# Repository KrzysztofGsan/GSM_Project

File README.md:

# GSM Home Controller (AVR) - Work in Progress

## Project Overview
This is an embedded C project developed for the **ATmega16** microcontroller. The primary objective is to create a versatile controller capable of managing electrical outputs based on various inputs, including **SMS commands (GSM module)**, **time-based scheduling (RTC)**, and **sound triggers (Clap Switch)**.

The project demonstrates a hands-on approach to low-level programming and hardware-software interaction in an embedded environment.

## Key Features & Tech Stack
* **State Machine Architecture:** Implemented a robust state machine (`enum Tryb`) to manage multiple operation modes (GSM, Bluetooth, Potentiometer control, Time Scheduling, and Sound Control).
* **Communication Protocols:**
    * **UART:** Integration with a GSM module using AT commands for remote control and message parsing.
    * **I2C (TWI):** Interfacing with a Real-Time Clock (DS1307/similar) for precise time-based output triggering.
* **Peripheral Management:**
    * **ADC:** Used for sound detection (Clap Switch logic) and reading analog values from potentiometers or sensors.
    * **PWM (Fast PWM Mode):** Power output control with adjustable duty cycle.
    * **Interrupts:** Efficient handling of serial data reception (USART_RX) and timer-based tasks (display refreshing).
* **Hardware:** AVR ATmega16, HD44780 LCD, GSM/BT modules, Triac/Relay outputs.
* **Environment:** Developed using **Eclipse IDE with AVR plugin**.

## Current Status
* [x] Hardware abstraction layer for GPIO, PWM, and ADC.
* [x] I2C Communication with RTC and time-matching logic.
* [x] Menu system for manual mode switching via hardware buttons.
* [x] Real-time status reporting on HD44780 LCD.
* [ ] **In Progress:** Refining the circular buffer logic for GSM message parsing and improving ASPICE-aligned documentation for the project.

## How to build
The project is configured for a CPU frequency of **8MHz** (defined in the IDE/Makefile). It requires the `avr-gcc` compiler and `avr-libc`.

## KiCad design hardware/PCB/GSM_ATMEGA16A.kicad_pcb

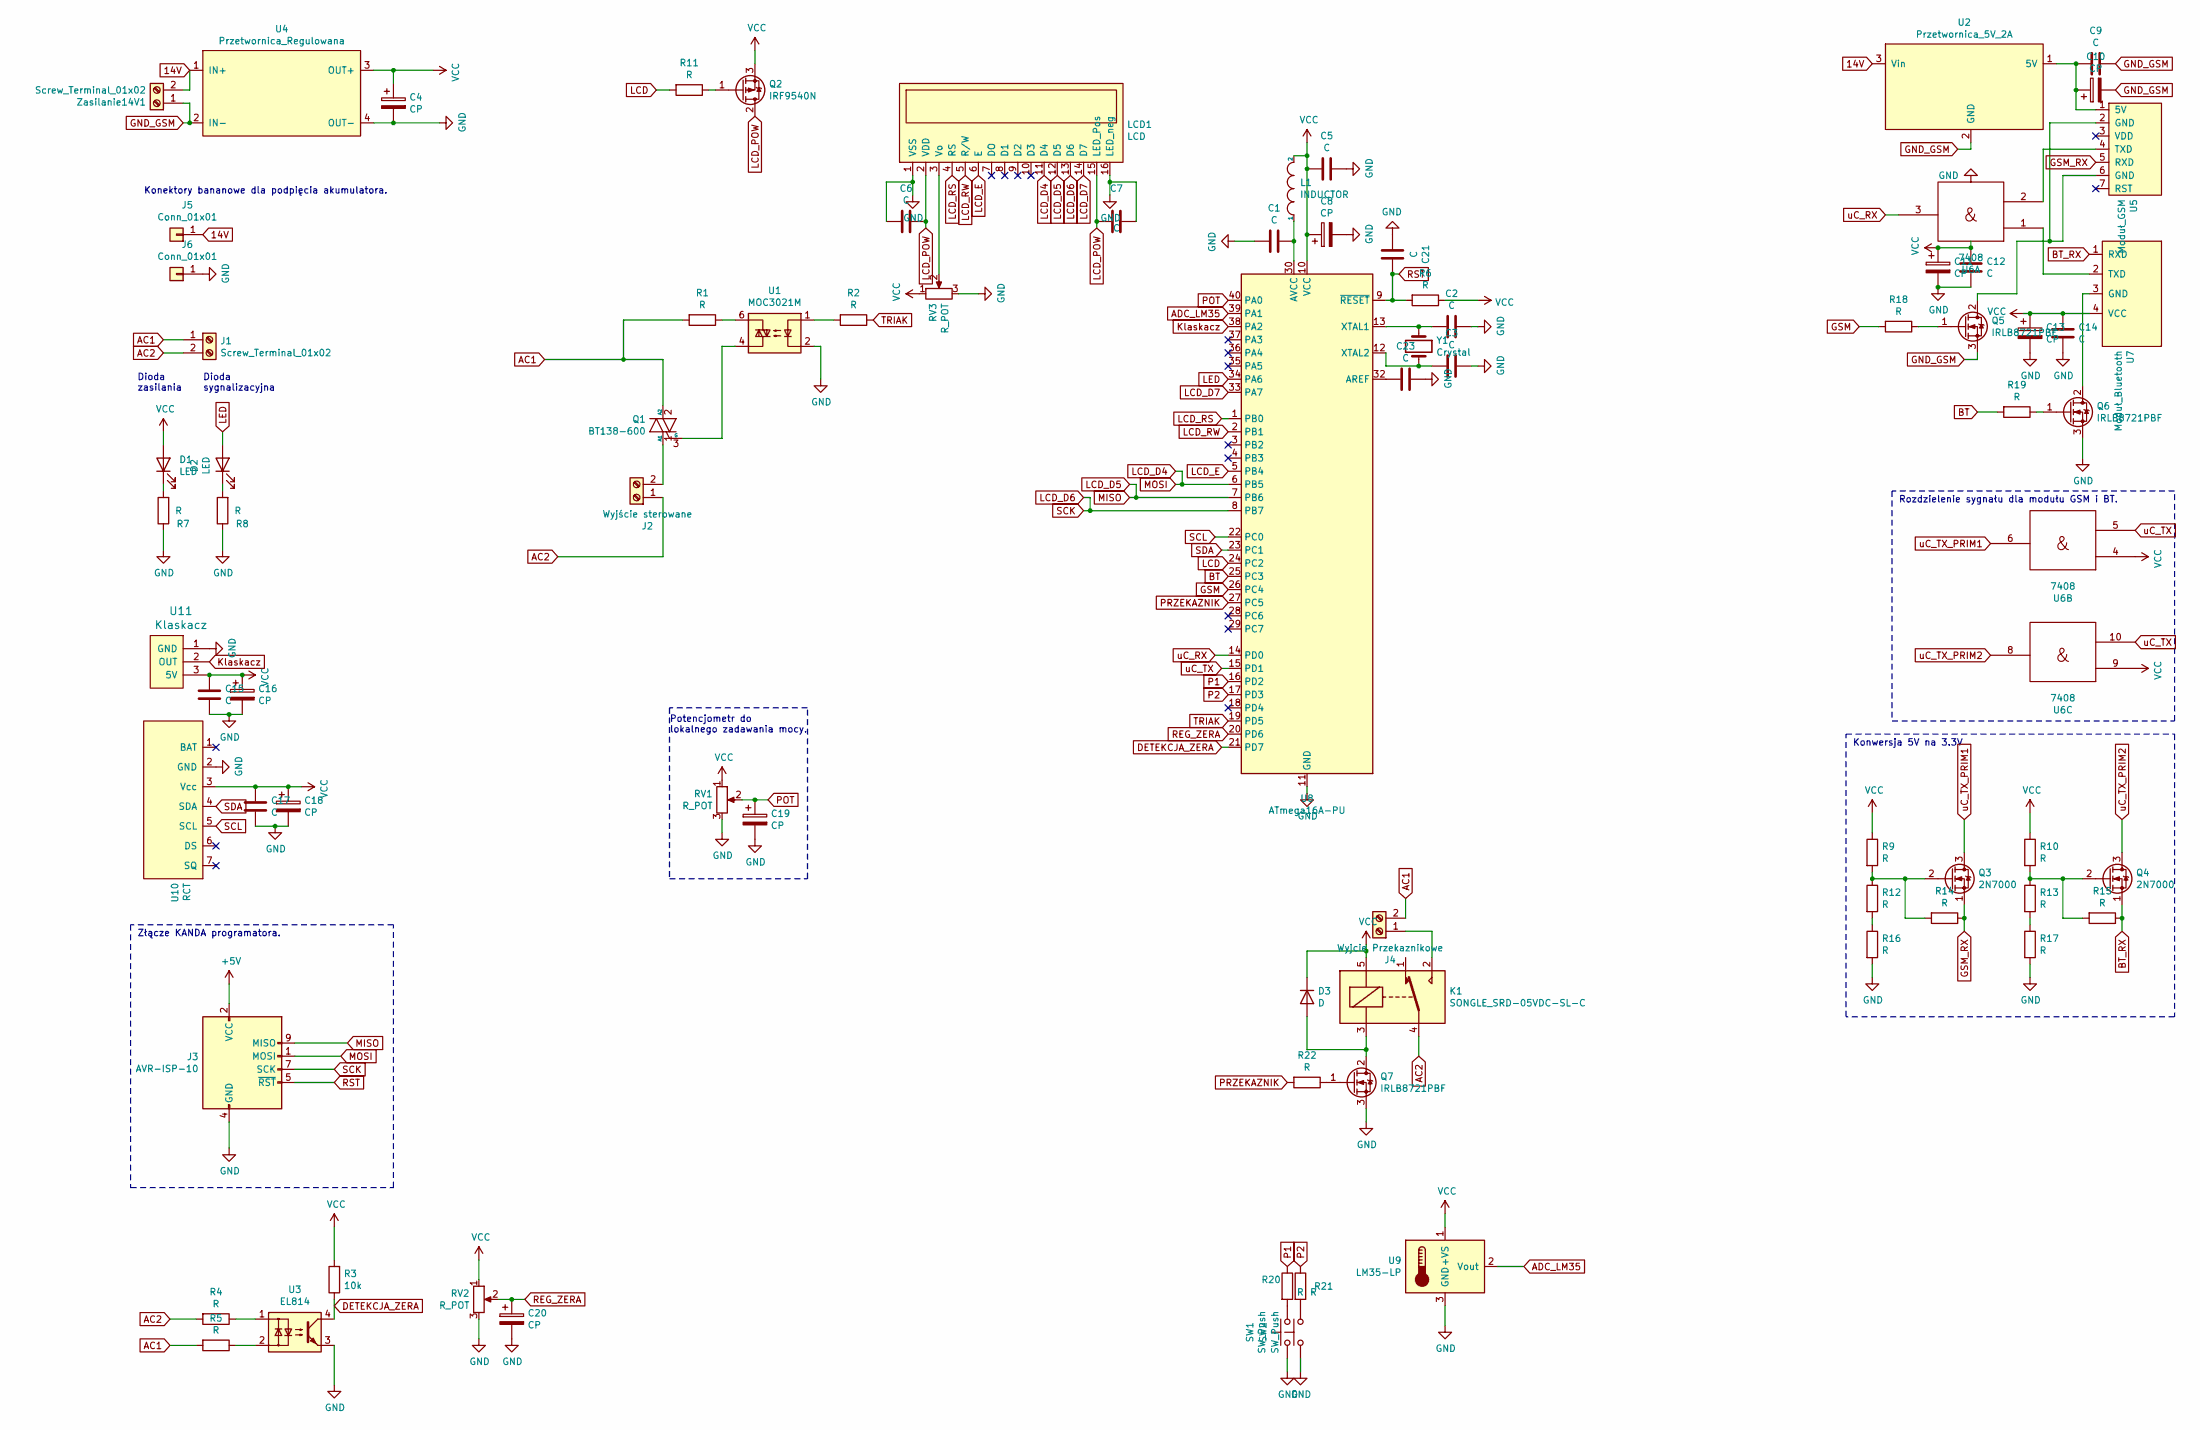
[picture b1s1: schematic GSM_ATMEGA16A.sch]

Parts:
C1, C21, C23: C; C_Disc_D5.0mm_W2.5mm_P5.00mm
C2, C3: C; C_Disc_D3.0mm_W1.6mm_P2.50mm
C4: CP; CP_Radial_D10.0mm_P3.50mm
C5, C6, C7, C9, C12, C14, C15, C17: C; C_Disc_D4.3mm_W1.9mm_P5.00mm
C8, C10, C11, C13, C16, C18, C19, C20: CP; CP_Radial_D4.0mm_P1.50mm
D1, D2: LED; LED_D5.0mm_Clear
D3: D; D_T-1_P10.16mm_Horizontal
J1: Screw_Terminal_01x02; TerminalBlock_bornier-2_P5.08mm
J2: Wyjście sterowane; TerminalBlock_bornier-2_P5.08mm
J3: AVR-ISP-10; IDC-Header_2x05_P2.54mm_Vertical
J4: Wyjcie Przekaznikowe; TerminalBlock_bornier-2_P5.08mm
J5, J6: Conn_01x01; Banana_Jack_1Pin
K1: SONGLE_SRD-05VDC-SL-C; Przekaznik_SRD-05VDC-SL-C
L1: INDUCTOR; L_Axial_L5.3mm_D2.2mm_P7.62mm_Horizontal_Vishay_IM-1
LCD1: LCD
Q1: BT138-600; TO-220-3_Vertical
Q2: IRF9540N; TO-220-3_Vertical
Q3, Q4: 2N7000; TO-92_Inline
Q5, Q6, Q7: IRLB8721PBF; TO-220-3_Vertical
R1, R4, R5: R; R_Axial_DIN0411_L9.9mm_D3.6mm_P12.70mm_Horizontal
R2, R6, R7, R8, R9, R10, R11, R12, R13, R14, R15, R16, R17, R18, R19, R20, R21, R22: R; R_Axial_DIN0207_L6.3mm_D2.5mm_P7.62mm_Horizontal
R3: 10k; R_Axial_DIN0207_L6.3mm_D2.5mm_P7.62mm_Horizontal
RV1: R_POT; Potentiometer_Omeg_PC16BU_Vertical
RV2, RV3: R_POT; Potentiometer_Runtron_RM-065_Vertical
SW1, SW2: SW_Push; SW_PUSH-12mm
U1: MOC3021M; DIP-6_W7.62mm_Socket
U2: Przetwornica_5V_2A
U3: EL814; DIP-4_W7.62mm_Socket
U4: Przetwornica_Regulowana; PrzetwornicaRegulowana
U5: Moduł_GSM; Modul_GSM
U6: 7408; DIP-14_W7.62mm
U7: Moduł_Bluetooth; Modul_BT
U8: ATmega16A-PU; DIP-40_W15.24mm
U9: LM35-LP; TO-92
U10: RCT
U11: Klaskacz
Y1: Crystal; Resonator-2Pin_W8.0mm_H3.5mm
Zasilanie14V1: Screw_Terminal_01x02; TerminalBlock_bornier-2_P5.08mm

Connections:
14V: J5.1, U2.3 (Vin), U4.1 (IN+), Zasilanie14V1.2
+5V: J3.2 (VCC)
AC1: J1.1, J4.2, Q1.2 (A2), R1.2, R5.2
AC2: J1.2, J2.1, K1.4, R4.2
ADC_LM35: U8.39 (PA1), U9.2 (Vout)
BT: R19.2, U8.25 (PC3)
BT_RX: Q4.1 (S), R15.1, U7.1 (RXD)
DETEKCJA_ZERA: R3.1, U3.4, U8.21 (PD7)
GND: C1.2, C2.1, C3.1, C4.2, C5.1, C6.2, C7.1, C8.2, C11.2, C12.1, C13.2, C14.1, C15.2, C16.2, C17.2, C18.2, C19.2, C20.2, C21.2, C23.1, J3.4 (GND), J3.6 (GND), J3.8 (GND), J3.10 (GND), J6.1, LCD1.1 (VSS), LCD1.16 (LED_neg), Q6.3 (S), Q7.3 (S), R7.1, R8.1, R16.2, R17.2, RV1.3, RV2.3, RV3.3, SW1.1, SW2.1, U1.2, U3.3, U4.4 (OUT-), U6.7 (Gnd), U8.11 (GND), U8.31 (GND), U9.3 (GND), U10.2 (GND), U11.1 (GND); also elsewhere on the board
GND_GSM: C9.1, C10.2, Q5.3 (S), U2.2 (GND), U4.2 (IN-), Zasilanie14V1.1
GSM: R18.2, U8.26 (PC4)
GSM_RX: Q3.1 (S), R14.1, U5.5 (RXD)
Klaskacz: U8.38 (PA2), U11.2 (OUT)
LCD: R11.2, U8.24 (PC2)
LCD_D4: J3.1 (MOSI), LCD1.11 (D4), U8.6 (PB5)
LCD_D5: J3.9 (MISO), LCD1.12 (D5), U8.7 (PB6)
LCD_D6: J3.7 (SCK), LCD1.13 (D6), U8.8 (PB7)
LCD_D7: LCD1.14 (D7), U8.33 (PA7)
LCD_E: LCD1.6 (E), U8.5 (PB4)
LCD_POW: C6.1, C7.2, LCD1.2 (VDD), LCD1.15 (LED_Pos), Q2.2 (D)
LCD_RS: LCD1.4 (RS), U8.1 (PB0)
LCD_RW: LCD1.5 (R/W), U8.2 (PB1)
LED: D2.2 (A), U8.34 (PA6)
unnamed: C1.1, L1.1, U8.30 (AVCC)
unnamed: C2.2, U8.13 (XTAL1), Y1.1
unnamed: C3.2, U8.12 (XTAL2), Y1.2
unnamed: C9.2, C10.1, U2.1 (5V), U5.1 (5V)
unnamed: C23.2, U8.32 (AREF)
unnamed: D1.1 (K), R7.2
unnamed: D2.1 (K), R8.2
unnamed: D3.2 (A), K1.3, Q7.2 (D)
unnamed: J2.2, Q1.1 (A1)
unnamed: J4.1, K1.2
unnamed: LCD1.3 (Vo), RV3.2
unnamed: Q1.3 (G), U1.4
unnamed: Q2.1 (G), R11.1
unnamed: Q3.2 (G), R9.2, R12.1, R14.2
unnamed: Q4.2 (G), R10.2, R13.1, R15.2
unnamed: Q5.1 (G), R18.1
unnamed: Q5.2 (D), U5.2 (GND), U5.6 (GND)
unnamed: Q6.1 (G), R19.1
unnamed: Q6.2 (D), U7.3 (GND)
unnamed: Q7.1 (G), R22.1
unnamed: R1.1, U1.6
unnamed: R2.2, U1.1
unnamed: R4.1, U3.1
unnamed: R5.1, U3.2
unnamed: R12.2, R16.1
unnamed: R13.2, R17.1
unnamed 55: R20.2, SW1.2; also elsewhere on the board
unnamed 56: R21.2, SW2.2; also elsewhere on the board
unnamed: U5.4 (TXD), U6.2
unnamed: U6.1, U7.2 (TXD)
P1: R20.1, U8.16 (PD2)
P2: R21.1, U8.17 (PD3)
POT: C19.1, RV1.2, U8.40 (PA0); also elsewhere on the board
PRZEKAZNIK: R22.2, U8.27 (PC5)
REG_ZERA: C20.1, RV2.2, U8.20 (PD6)
RST: C21.1, J3.5 (~RST), R6.2, U8.9 (~RESET)
SCL: U8.22 (PC0), U10.5 (SCL)
SDA: U8.23 (PC1), U10.4 (SDA)
TRIAK: R2.1, U8.19 (PD5)
VCC: C4.1, C5.2, C8.1, C11.1, C12.2, C13.1, C14.2, C15.1, C16.1, C17.1, C18.1, D1.2 (A), D3.1 (K), K1.5, L1.2, Q2.3 (S), R3.2, R6.1, R9.1, R10.1, RV1.1, RV2.1, RV3.1, U4.3 (OUT+), U6.4, U6.9, U6.14 (Vcc), U7.4 (VCC), U8.10 (VCC), U9.1 (+VS), U10.3 (Vcc), U11.3 (5V); also elsewhere on the board
uC_RX: U6.3, U8.14 (PD0)
uC_TX: U6.5, U6.10, U8.15 (PD1)
uC_TX_PRIM1: Q3.3 (D), U6.6
uC_TX_PRIM2: Q4.3 (D), U6.8

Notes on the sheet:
Rozdzielenie sygnału dla modułu GSM i BT.
Konwersja 5V na 3.3V
Potencjometr do lokalnego zadawania mocy.
Złącze KANDA programatora.
Dioda zasilania
Dioda sygnalizacyjna
Konektory bananowe dla podpięcia akumulatora.

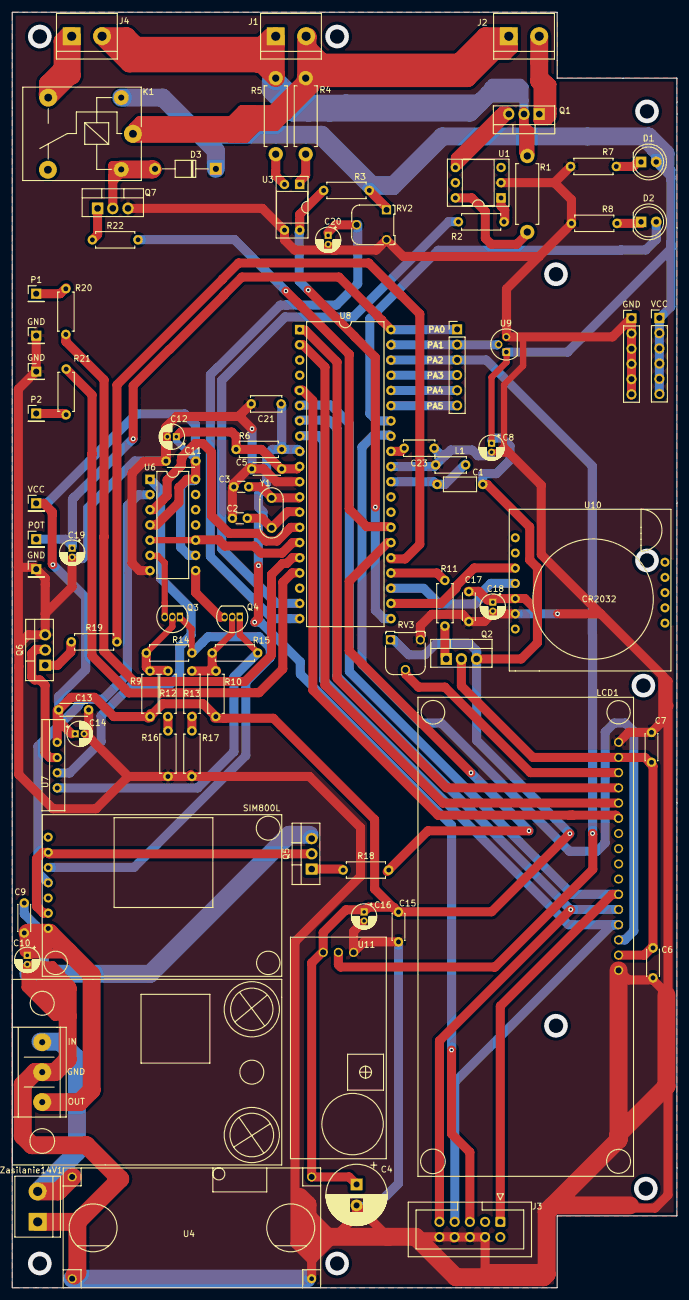
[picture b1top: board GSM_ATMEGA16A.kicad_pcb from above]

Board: 2 copper layers, 111.0 x 213.0 mm, 85 parts (0 on the bottom side), 66 nets.

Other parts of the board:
GND: PinHeader_1x06_P2.54mm_Vertical
GND#2, GND#3, GND#4: PinHeader_1x01_P2.54mm_Vertical
P1, P2: PinHeader_1x01_P2.54mm_Vertical
POT: PinHeader_1x01_P2.54mm_Vertical
VCC: PinHeader_1x06_P2.54mm_Vertical
VCC#2: PinHeader_1x01_P2.54mm_Vertical

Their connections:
GND: GND#2.1, GND#3.1, GND#4.1; also elsewhere on the board
unnamed 55: P1.1; also elsewhere on the board
unnamed 56: P2.1; also elsewhere on the board
POT: POT.1; also elsewhere on the board
VCC: VCC#2.1; also elsewhere on the board

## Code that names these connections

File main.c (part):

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#include <ctype.h>

#define PRESKALER 1
#define TRIAK PD5
#define PRZEKAZNIK PC5
#define MODUL_GSM PC4
#define MODUL_BT PC3
#define WYSWIETLACZ_LCD PC2
#define LED PA6
#define ADC_POT PC3
#define ADC_LM35 PC0
#define KLASKACZ PA2
#define PRZYCISK_ZATRZYMAJ (1<<PD2)
#define PRZYCISK_TRYBU (1<<PD3)
#define TRUE 1
#define FALSE 0
#define PIN_PRZYCISKOW PIND
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#define ROZMIAR_BUFORA 64

enum Tryb {
    FORCE_OFF = 0, PRE_GSM = 1, GSM = 2, PRE_BT = 4, BT = 5,
    PRE_POT = 6, POT = 7, PRE_STOP = 8, ON_MIN_SET = 9, ON_HOUR_SET = 10,
    OFF_MIN_SET = 11, OFF_HOUR_SET = 12, TIME_CONTROL = 13, FORCE_ON = 14,
    FORCE_ON_SET = 15, KLASK_CONTROL = 16, KLASK_CONTROL_SET = 17
};
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
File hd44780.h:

/*
Plik hd44780.h
*/

#ifndef LCD_HD44780
#define LCD_HD44780

/* RS */
#define SET_OUT_LCD_RS  DDRB  |=  _BV(PB0)
#define SET_LCD_RS      PORTB |=  _BV(PB0)
#define CLR_LCD_RS      PORTB &= ~_BV(PB0)

/* RW */
#define SET_OUT_LCD_RW  DDRB  |=  _BV(PB1)
#define SET_LCD_RW      PORTB |=  _BV(PB1)
#define CLR_LCD_RW      PORTB &= ~_BV(PB1)

/* E */
#define SET_OUT_LCD_E   DDRB  |=  _BV(PB4)
#define SET_LCD_E       PORTB |=  _BV(PB4)
#define CLR_LCD_E       PORTB &= ~_BV(PB4)

/* D4 */
#define SET_OUT_LCD_D4  DDRB  |=  _BV(PB5)
#define SET_IN_LCD_D4   DDRB  &= ~_BV(PB5)
#define SET_LCD_D4      PORTB |=  _BV(PB5)
#define CLR_LCD_D4      PORTB &= ~_BV(PB5)
#define IS_SET_LCD_D4   PINB  &   _BV(PB5)

/* D5 */
#define SET_OUT_LCD_D5  DDRB  |=  _BV(PB6)
#define SET_IN_LCD_D5   DDRB  &= ~_BV(PB6)
#define SET_LCD_D5      PORTB |=  _BV(PB6)
#define CLR_LCD_D5      PORTB &= ~_BV(PB6)
#define IS_SET_LCD_D5   PINB  &   _BV(PB6)

/* D6 */
#define SET_OUT_LCD_D6  DDRB  |=  _BV(PB7)
#define SET_IN_LCD_D6   DDRB  &= ~_BV(PB7)
#define SET_LCD_D6      PORTB |=  _BV(PB7)
#define CLR_LCD_D6      PORTB &= ~_BV(PB7)
#define IS_SET_LCD_D6   PINB  &   _BV(PB7)

/* D7 */
#define SET_OUT_LCD_D7  DDRA  |=  _BV(PA7)
#define SET_IN_LCD_D7   DDRA  &= ~_BV(PA7)
#define SET_LCD_D7      PORTA |=  _BV(PA7)
#define CLR_LCD_D7      PORTA &= ~_BV(PA7)
#define IS_SET_LCD_D7   PINA  &   _BV(PA7)


#define LCD_NOP asm volatile("nop\n\t""nop\n\t" "nop\n\t" "nop\n\t" ::);



#define LCDCOMMAND 0
#define LCDDATA    1

#define LCD_LOCATE(x,y)  WriteToLCD(0x80|((x)+((y)*0x40)), LCDCOMMAND)

#define LCD_CLEAR              WriteToLCD(0x01, LCDCOMMAND)
#define LCD_HOME               WriteToLCD(0x02, LCDCOMMAND)

/* IDS */

#define LCDINCREMENT           0x02
#define LCDDECREMENT           0x00
#define LCDDISPLAYSHIFT        0x01

#define LCD_ENTRY_MODE(IDS)    WriteToLCD(0x04|(IDS), LCDCOMMAND)

/* BCD */
#define LCDDISPLAY             0x04
#define LCDCURSOR              0x02
#define LCDBLINK               0x01

#define LCD_DISPLAY(DCB)       WriteToLCD(0x08|(DCB), LCDCOMMAND)

/* RL */
#define LCDLEFT                0x00
#define LCDRIGHT               0x04

#define LCD_SHIFT_DISPLAY(RL)  WriteToLCD(0x18|(RL), LCDCOMMAND)
#define LCD_SHIFT_CURSOR(RL)   WriteToLCD(0x10|(RL), LCDCOMMAND)

#define LCD_CGRAM_ADDRESS(A)   WriteToLCD(0x40|((A)&0x3f), LCDCOMMAND)
#define LCD_DDRAM_ADDRESS(A)   WriteToLCD(0x80|((A)&0x7f), LCDCOMMAND)

#define LCD_WRITE_DATA(D)      WriteToLCD((D),LCDDATA)


void lcd_init(void);
void WriteToLCD(unsigned char v,unsigned char rs);
unsigned char ReadAddressLCD(void);
void lcd_puts(char *str);

#endif

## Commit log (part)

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2023-12-03 dziala zal/wyl o wybranej godzine
2023-12-03 dodano obluge przyciskow
2023-12-03 poprawa wyswietlania malych liczb
2023-12-17 dodanie miganie ustawianej minuty/godziny
2024-01-08 modyfikacja Obsluga_Przyciskow
2024-01-08 mozna ustawic zarowno godzine zal jak i wyl
2024-01-08 przywrocono wyswielanie godziny
2024-01-28 dodano wylacznik awaryjny
2024-02-05 koretka w Przyciski_Init
2024-02-05 wersja debugowana
2024-02-10 dobry program! stop awaryjny dziala
2024-02-10 dodano podtrzymanie stopa gdy nic nie jest nacisniete
2024-02-10 dodano force on
2024-02-11 korekty wyswietlania i obslugi przycisku ZATRZYMAJ. Na prawde dobry program
2024-02-11 dodano ustawianie sekund (zakomentowano) DOBRY PROGRAM
2024-02-11 zmieniono poczatkowy tryb na FORCE ON. DOBRY PROGRAM
2024-03-18 ADC - dodanie klaskacza. temp
2024-03-18 poprawa klaskacza
2024-04-22 rozwiazano problem podwojnej reakcji na klasniecie
2024-05-22 program przebudowano
2024-05-22 program przebudowano. DOBRY!
2026-04-01 KGR: zmiany w git ignore
2026-04-22 Initialize README with project details and instructions
    Added project overview, key features, current status, and build instructions to README.
2026-05-25 KGR: dodano pliki KiCad
2026-05-27 baseline przed poprawkami
